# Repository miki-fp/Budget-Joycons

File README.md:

# Budget-Joycons
Custom Split Controller, inspired by Nintendo Joycons

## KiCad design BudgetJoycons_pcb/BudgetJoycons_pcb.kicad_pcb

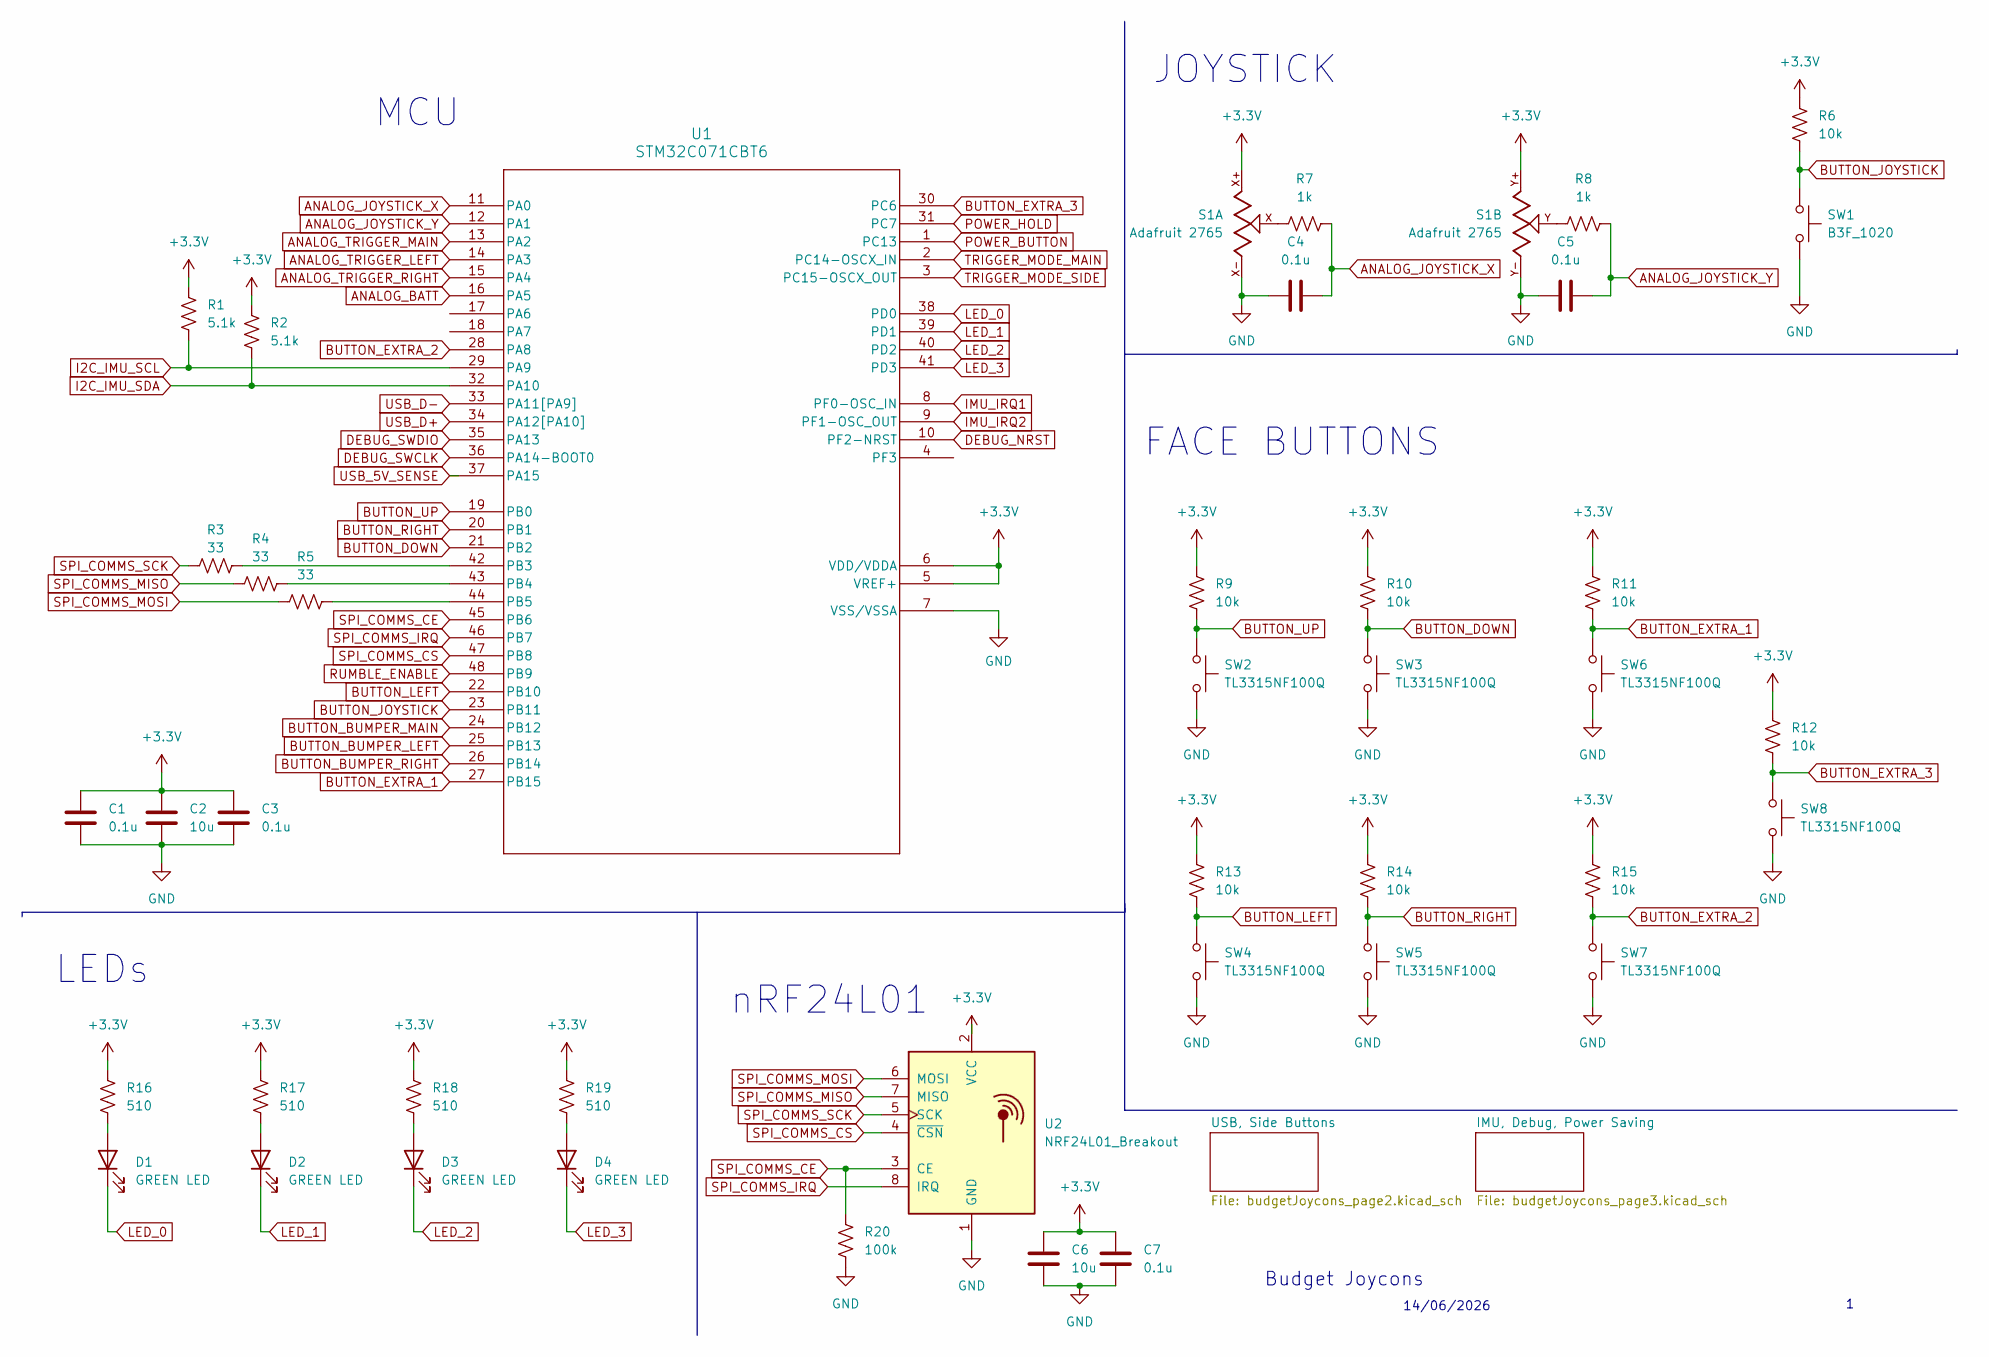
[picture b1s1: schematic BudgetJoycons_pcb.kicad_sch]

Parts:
C1, C3, C4, C5, C7: 0.1u; C_0603_1608Metric_Pad1.08x0.95mm_HandSolder
C2, C6: 10u; C_0805_2012Metric_Pad1.18x1.45mm_HandSolder
D1, D2, D3, D4: GREEN LED; LED_0805_2012Metric_Pad1.15x1.40mm_HandSolder
R1, R2: 5.1k; R_0603_1608Metric_Pad0.98x0.95mm_HandSolder
R3, R4, R5: 33; R_0603_1608Metric_Pad0.98x0.95mm_HandSolder
R6, R9, R10, R11, R12, R13, R14, R15: 10k; R_0603_1608Metric_Pad0.98x0.95mm_HandSolder
R7, R8: 1k; R_0603_1608Metric_Pad0.98x0.95mm_HandSolder
R16, R17, R18, R19: 510; R_0805_2012Metric_Pad1.20x1.40mm_HandSolder
R20: 100k; R_0603_1608Metric_Pad0.98x0.95mm_HandSolder
S1: Adafruit 2765; Adafruit_Joystick_2765
SW1: B3F_1020; B3F-1020
SW2, SW3, SW4, SW5, SW6, SW7, SW8: TL3315NF100Q; SW_TL3315NF100Q
U1: STM32C071CBT6; LQFP48_1_STM-M
U2: NRF24L01_Breakout; nRF24L01_Breakout

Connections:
+3.3V: C1.1, C2.1, C3.1, C6.1, C7.1, R1.1, R2.1, R6.1, R9.1, R10.1, R11.1, R12.1, R13.1, R14.1, R15.1, R16.1, R17.1, R18.1, R19.1, S1.X+, S1.Y+, U1.5 (VREF+), U1.6 (VDD/VDDA), U2.2 (VCC); also elsewhere on the board
ANALOG_BATT: U1.16 (PA5); also elsewhere on the board
ANALOG_JOYSTICK_X: C4.2, R7.2, U1.11 (PA0)
ANALOG_JOYSTICK_Y: C5.2, R8.2, U1.12 (PA1)
ANALOG_TRIGGER_LEFT: U1.14 (PA3); also elsewhere on the board
ANALOG_TRIGGER_MAIN: U1.13 (PA2); also elsewhere on the board
ANALOG_TRIGGER_RIGHT: U1.15 (PA4); also elsewhere on the board
BUTTON_BUMPER_LEFT: U1.25 (PB13); also elsewhere on the board
BUTTON_BUMPER_MAIN: U1.24 (PB12); also elsewhere on the board
BUTTON_BUMPER_RIGHT: U1.26 (PB14); also elsewhere on the board
BUTTON_DOWN: R10.2, SW3.1, U1.21 (PB2)
BUTTON_EXTRA_1: R11.2, SW6.1, U1.27 (PB15)
BUTTON_EXTRA_2: R15.2, SW7.1, U1.28 (PA8)
BUTTON_EXTRA_3: R12.2, SW8.1, U1.30 (PC6)
BUTTON_JOYSTICK: R6.2, SW1.1, U1.23 (PB11)
BUTTON_LEFT: R13.2, SW4.1, U1.22 (PB10)
BUTTON_RIGHT: R14.2, SW5.1, U1.20 (PB1)
BUTTON_UP: R9.2, SW2.1, U1.19 (PB0)
DEBUG_NRST: U1.10 (PF2-NRST); also elsewhere on the board
DEBUG_SWCLK: U1.36 (PA14-BOOT0); also elsewhere on the board
DEBUG_SWDIO: U1.35 (PA13); also elsewhere on the board
GND: C1.2, C2.2, C3.2, C4.1, C5.1, C6.2, C7.2, R20.2, S1.X-, S1.Y-, SW1.2, SW2.2, SW3.2, SW4.2, SW5.2, SW6.2, SW7.2, SW8.2, U1.7 (VSS/VSSA), U2.1 (GND); also elsewhere on the board
I2C_IMU_SCL: R1.2, U1.29 (PA9); also elsewhere on the board
I2C_IMU_SDA: R2.2, U1.32 (PA10); also elsewhere on the board
IMU_IRQ1: U1.8 (PF0-OSC_IN); also elsewhere on the board
IMU_IRQ2: U1.9 (PF1-OSC_OUT); also elsewhere on the board
LED_0: D1.1 (K), U1.38 (PD0)
LED_1: D2.1 (K), U1.39 (PD1)
LED_2: D3.1 (K), U1.40 (PD2)
LED_3: D4.1 (K), U1.41 (PD3)
unnamed: D1.2 (A), R16.2
unnamed: D2.2 (A), R17.2
unnamed: D3.2 (A), R18.2
unnamed: D4.2 (A), R19.2
unnamed: R7.1, S1.X
unnamed: R8.1, S1.Y
unnamed: R3.1, U1.42 (PB3)
unnamed: R4.1, U1.43 (PB4)
unnamed: R5.1, U1.44 (PB5)
POWER_BUTTON: U1.1 (PC13); also elsewhere on the board
POWER_HOLD: U1.31 (PC7); also elsewhere on the board
RUMBLE_ENABLE: U1.48 (PB9); also elsewhere on the board
SPI_COMMS_CE: R20.1, U1.45 (PB6), U2.3 (CE)
SPI_COMMS_CS: U1.47 (PB8), U2.4 (~CSN)
SPI_COMMS_IRQ: U1.46 (PB7), U2.8 (IRQ)
SPI_COMMS_MISO: R4.2, U2.7 (MISO)
SPI_COMMS_MOSI: R5.2, U2.6 (MOSI)
SPI_COMMS_SCK: R3.2, U2.5 (SCK)
TRIGGER_MODE_MAIN: U1.2 (PC14-OSCX_IN); also elsewhere on the board
TRIGGER_MODE_SIDE: U1.3 (PC15-OSCX_OUT); also elsewhere on the board
USB_5V_SENSE: U1.37 (PA15); also elsewhere on the board
USB_D+: U1.34 (PA12[PA10]); also elsewhere on the board
USB_D-: U1.33 (PA11[PA9]); also elsewhere on the board

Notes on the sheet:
14/06/2026
FACE BUTTONS
MCU
JOYSTICK
Budget Joycons
LEDs
nRF24L01

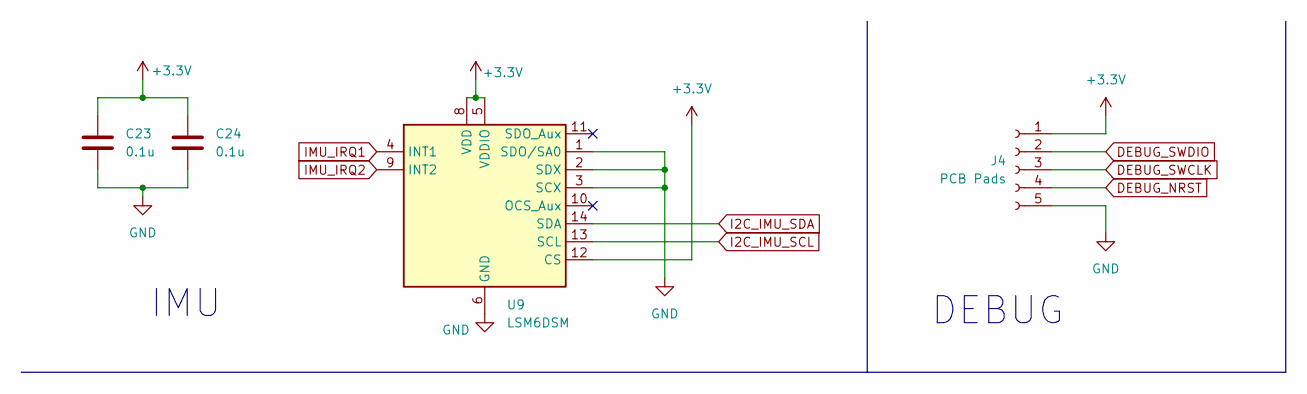
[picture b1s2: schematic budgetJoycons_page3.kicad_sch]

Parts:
C23, C24: 0.1u; C_0603_1608Metric_Pad1.08x0.95mm_HandSolder
J4: PCB Pads; Edge_2.54mm_Pads
U9: LSM6DSM; LGA-14_3x2.5mm_P0.5mm_LayoutBorder3x4y

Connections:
+3.3V: C23.2, C24.2, J4.1, U9.5 (VDDIO), U9.8 (VDD), U9.12 (CS); also elsewhere on the board
DEBUG_NRST: J4.4; also elsewhere on the board
DEBUG_SWCLK: J4.3; also elsewhere on the board
DEBUG_SWDIO: J4.2; also elsewhere on the board
GND: C23.1, C24.1, J4.5, U9.1 (SDO/SA0), U9.2 (SDX), U9.3 (SCX), U9.6 (GND), U9.7 (GND); also elsewhere on the board
I2C_IMU_SCL: U9.13 (SCL); also elsewhere on the board
I2C_IMU_SDA: U9.14 (SDA); also elsewhere on the board
IMU_IRQ1: U9.4 (INT1); also elsewhere on the board
IMU_IRQ2: U9.9 (INT2); also elsewhere on the board

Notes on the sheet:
DEBUG
IMU

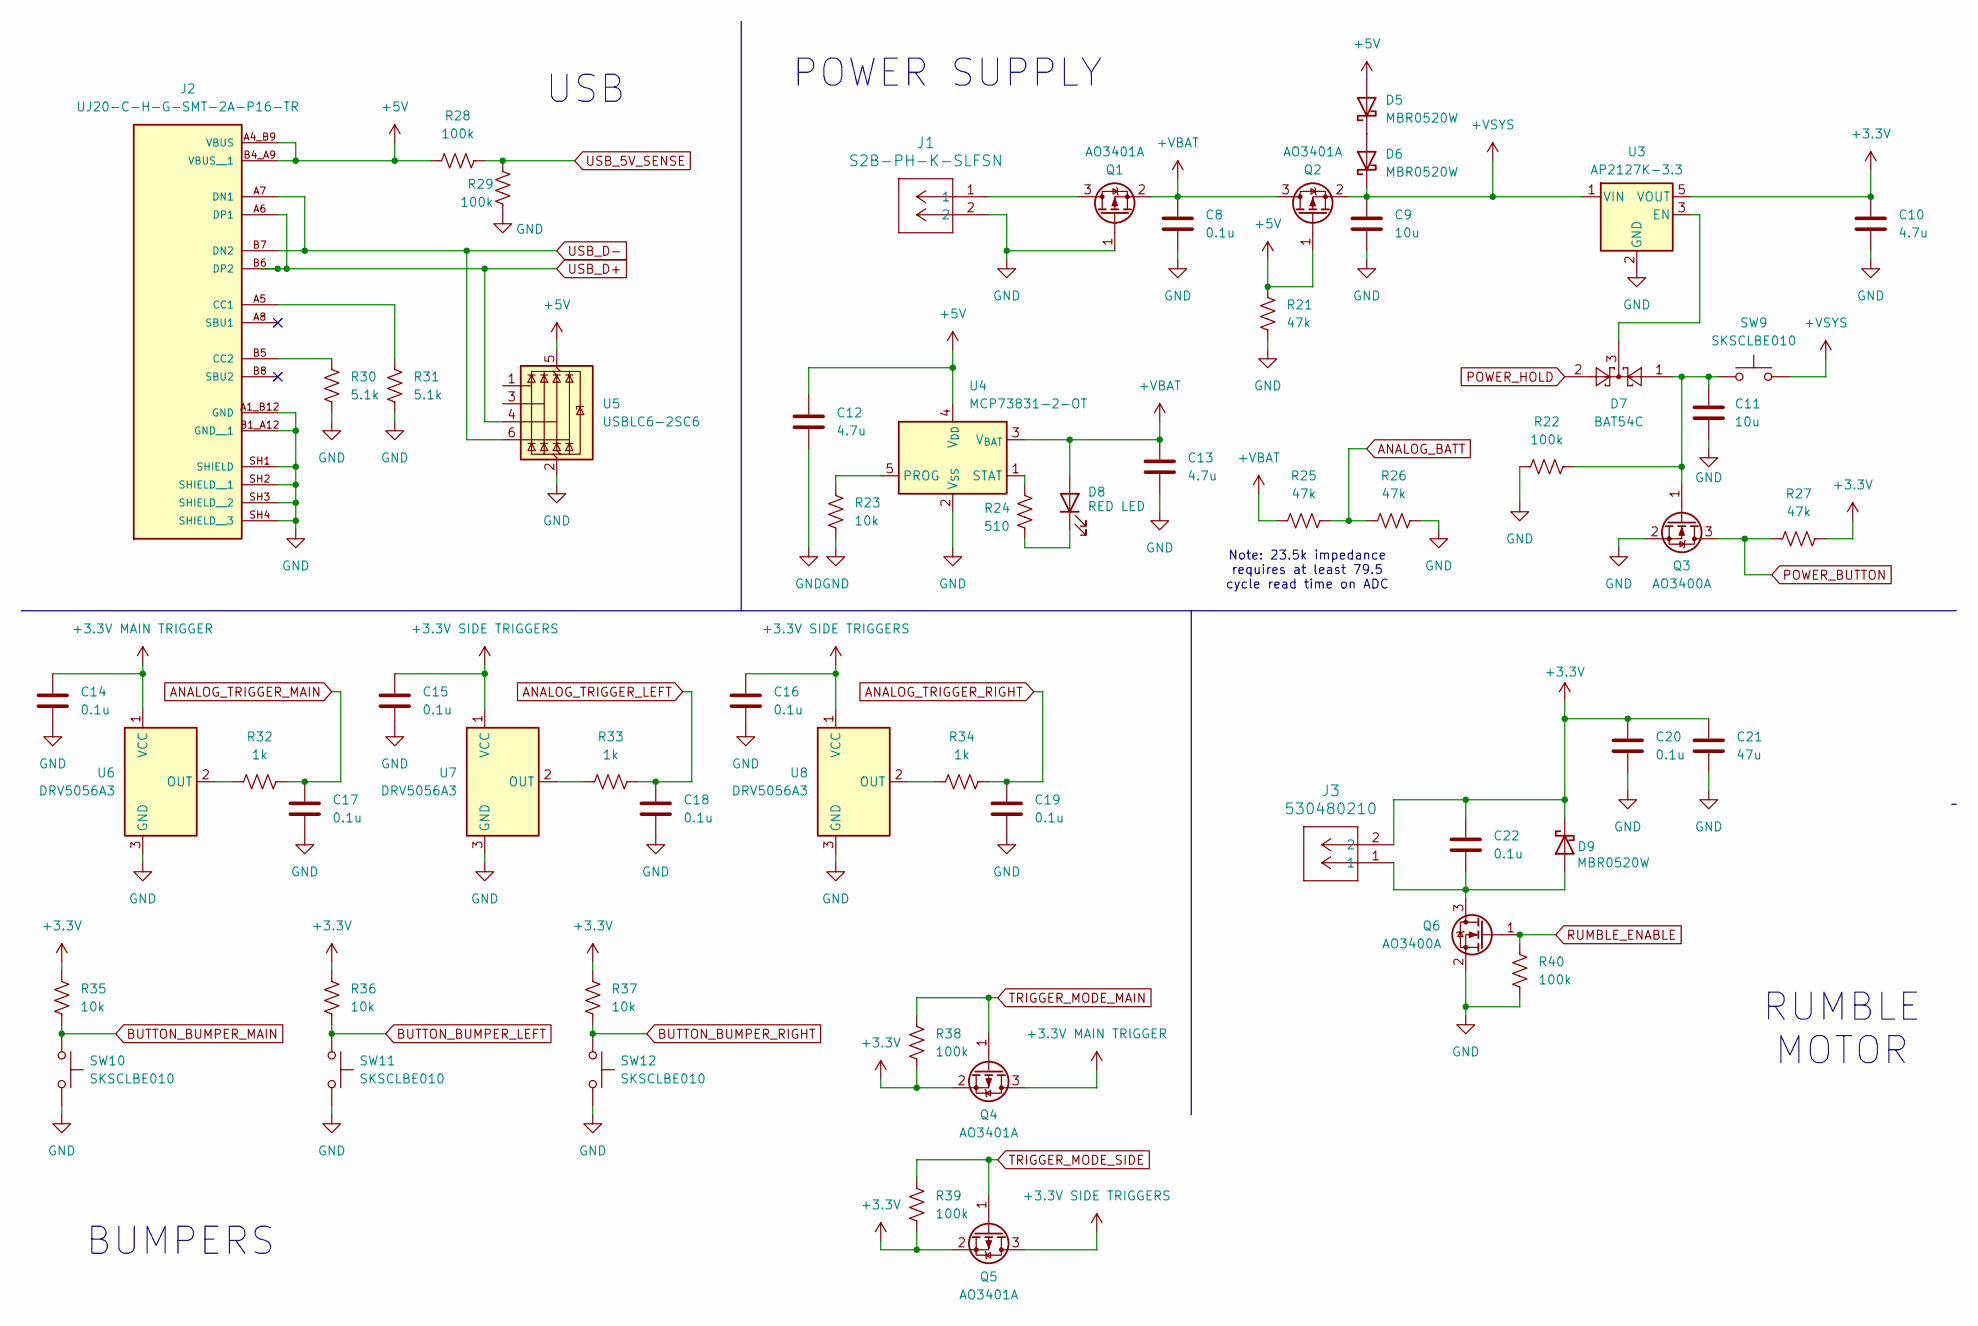
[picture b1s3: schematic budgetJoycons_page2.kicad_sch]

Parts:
C8, C14, C15, C16, C17, C18, C19, C20, C22: 0.1u; C_0603_1608Metric_Pad1.08x0.95mm_HandSolder
C9, C11: 10u; C_0805_2012Metric_Pad1.18x1.45mm_HandSolder
C10, C12, C13: 4.7u; C_0603_1608Metric_Pad1.08x0.95mm_HandSolder
C21: 47u; C_1206_3216Metric_Pad1.33x1.80mm_HandSolder
D5, D6, D9: MBR0520W; D_SOD-123
D7: BAT54C; SOT-23
D8: RED LED; LED_0805_2012Metric_Pad1.15x1.40mm_HandSolder
J1: S2B-PH-K-SLFSN; CONN_S2B-PH-K-S_JST
J2: UJ20-C-H-G-SMT-2A-P16-TR; SAMESKY_UJ20-C-H-G-SMT-2A-P16-TR; PARTREV 1.0
J3: 530480210; CONN02_530480210_MOL
Q1, Q2, Q4, Q5: AO3401A; SOT-23
Q3, Q6: AO3400A; SOT-23
R21, R25, R26, R27: 47k; R_0603_1608Metric_Pad0.98x0.95mm_HandSolder
R22, R28, R29, R38, R39, R40: 100k; R_0603_1608Metric_Pad0.98x0.95mm_HandSolder
R23, R35, R36, R37: 10k; R_0603_1608Metric_Pad0.98x0.95mm_HandSolder
R24: 510; R_0805_2012Metric_Pad1.20x1.40mm_HandSolder
R30, R31: 5.1k; R_0603_1608Metric_Pad0.98x0.95mm_HandSolder
R32, R33, R34: 1k; R_0603_1608Metric_Pad0.98x0.95mm_HandSolder
SW9, SW10, SW11, SW12: SKSCLBE010; SKSCLDE010
U3: AP2127K-3.3; SOT-23-5
U4: MCP73831-2-OT; SOT-23-5
U5: USBLC6-2SC6; SOT-23-6
U6, U7, U8: DRV5056A3; SOT-23-3

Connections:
+3.3V: C10.1, C20.1, C21.1, C22.1, D9.1 (K), J3.2, Q4.2 (S), Q5.2 (S), R27.2, R35.1, R36.1, R37.1, R38.2, R39.2, U3.5 (VOUT); also elsewhere on the board
+3.3V MAIN TRIGGER: C14.1, Q4.3 (D), U6.1 (VCC)
+3.3V SIDE TRIGGERS: C15.1, C16.1, Q5.3 (D), U7.1 (VCC), U8.1 (VCC)
+5V: C12.1, D5.2 (A), J2.A4_B9 (VBUS), J2.B4_A9 (VBUS__1), Q2.1 (G), R21.1, R28.2, U4.4 (V_{DD}), U5.5 (VBUS)
+VBAT: C8.1, C13.1, D8.2 (A), Q1.2 (S), Q2.3 (D), R25.1, U4.3 (V_{BAT})
+VSYS: C9.1, D6.1 (K), Q2.2 (S), SW9.2, U3.1 (VIN)
ANALOG_BATT: R25.2, R26.2; also elsewhere on the board
ANALOG_TRIGGER_LEFT: C18.1, R33.2; also elsewhere on the board
ANALOG_TRIGGER_MAIN: C17.1, R32.2; also elsewhere on the board
ANALOG_TRIGGER_RIGHT: C19.1, R34.2; also elsewhere on the board
BUTTON_BUMPER_LEFT: R36.2, SW11.1; also elsewhere on the board
BUTTON_BUMPER_MAIN: R35.2, SW10.1; also elsewhere on the board
BUTTON_BUMPER_RIGHT: R37.2, SW12.1; also elsewhere on the board
GND: C8.2, C9.2, C10.2, C11.2, C12.2, C13.2, C14.2, C15.2, C16.2, C17.2, C18.2, C19.2, C20.2, C21.2, J1.2, J2.A1_B12 (GND), J2.B1_A12 (GND__1), J2.SH1 (SHIELD), J2.SH2 (SHIELD__1), J2.SH3 (SHIELD__2), J2.SH4 (SHIELD__3), Q1.1 (G), Q3.2 (S), Q6.2 (S), R21.2, R22.1, R23.2, R26.1, R29.2, R30.2, R31.2, R40.2, SW10.2, SW11.2, SW12.2, U3.2 (GND), U4.2 (V_{SS}), U5.2 (GND), U6.3 (GND), U7.3 (GND), U8.3 (GND); also elsewhere on the board
unnamed: D5.1 (K), D6.2 (A)
unnamed: D8.1 (K), R24.2
unnamed: C22.2, D9.2 (A), J3.1, Q6.3 (D)
unnamed: J2.A5 (CC1), R31.1
unnamed: J2.B5 (CC2), R30.1
unnamed: J1.1, Q1.3 (D)
unnamed: C11.1, D7.1, Q3.1 (G), R22.2, SW9.1
unnamed: D7.3, U3.3 (EN)
unnamed: R23.1, U4.5 (PROG)
unnamed: R24.1, U4.1 (STAT)
unnamed: R32.1, U6.2 (OUT)
unnamed: R33.1, U7.2 (OUT)
unnamed: R34.1, U8.2 (OUT)
POWER_BUTTON: Q3.3 (D), R27.1; also elsewhere on the board
POWER_HOLD: D7.2; also elsewhere on the board
RUMBLE_ENABLE: Q6.1 (G), R40.1; also elsewhere on the board
TRIGGER_MODE_MAIN: Q4.1 (G), R38.1; also elsewhere on the board
TRIGGER_MODE_SIDE: Q5.1 (G), R39.1; also elsewhere on the board
USB_5V_SENSE: R28.1, R29.1; also elsewhere on the board
USB_D+: J2.A6 (DP1), J2.B6 (DP2), U5.4 (I/O3); also elsewhere on the board
USB_D-: J2.A7 (DN1), J2.B7 (DN2), U5.6 (I/O4); also elsewhere on the board

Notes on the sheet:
BUMPERS
USB
POWER SUPPLY
Note: 23.5k impedance requires at least 79.5 cycle read time on ADC
RUMBLE MOTOR

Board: 4 copper layers, 105 parts (37 on the bottom side), 71 nets, no tracks yet.

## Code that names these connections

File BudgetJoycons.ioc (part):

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Mcu.Name=STM32C071CBTx
Mcu.Package=LQFP48_GP
Mcu.UserName=STM32C071CBTx
PA0.GPIOParameters=GPIO_Label
PA0.GPIO_Label=ANALOG_JOYSTICK_X
PA0.Mode=IN0
PA0.Signal=ADC1_IN0
PA1.GPIOParameters=GPIO_Label
PA1.GPIO_Label=ANALOG_JOYSTICK_Y
PA1.Mode=IN1
PA1.Signal=ADC1_IN1
PA10.GPIOParameters=GPIO_Label
PA10.GPIO_Label=I2C_IMU_SDA
PA10.Mode=I2C
PA10.Signal=I2C1_SDA
PA11\ [PA9].Mode=Device
PA11\ [PA9].Signal=USB_DM
PA12\ [PA10].Mode=Device
PA12\ [PA10].Signal=USB_DP
PA13.Mode=Serial_Wire
PA13.Signal=DEBUG_SWDIO
PA14-BOOT0.Mode=Serial_Wire
PA14-BOOT0.Signal=DEBUG_SWCLK
PA15.GPIOParameters=GPIO_Label
PA15.GPIO_Label=USB_5V_SENSE
PA15.Signal=GPIO_Input
PA2.GPIOParameters=GPIO_Label
PA2.GPIO_Label=ANALOG_TRIGGER_MAIN
PA2.Mode=IN2
PA2.Signal=ADC1_IN2
PA3.GPIOParameters=GPIO_Label
PA3.GPIO_Label=ANALOG_TRIGGER_LEFT
PA3.Mode=IN3
PA3.Signal=ADC1_IN3
PA4.GPIOParameters=GPIO_Label
PA4.GPIO_Label=ANALOG_TRIGGER_RIGHT
PA4.Mode=IN4
PA4.Signal=ADC1_IN4
PA5.GPIOParameters=GPIO_Label
PA5.GPIO_Label=ANALOG_BATT
PA5.Mode=IN5
PA5.Signal=ADC1_IN5
PA8.GPIOParameters=GPIO_Label
PA8.GPIO_Label=BUTTON_EXTRA_2
PA8.Signal=GPIO_Input
PA9.GPIOParameters=GPIO_Label
PA9.GPIO_Label=I2C_IMU_SCL
PA9.Mode=I2C
PA9.Signal=I2C1_SCL
PB0.GPIOParameters=GPIO_Label
PB0.GPIO_Label=BUTTON_UP
PB0.Signal=GPIO_Input
PB1.GPIOParameters=GPIO_Label
PB1.GPIO_Label=BUTTON_RIGHT
PB1.Signal=GPIO_Input
PB10.GPIOParameters=GPIO_Label
PB10.GPIO_Label=BUTTON_LEFT
PB10.Signal=GPIO_Input
PB11.GPIOParameters=GPIO_Label
PB11.GPIO_Label=BUTTON_JOYSTICK
PB11.Signal=GPIO_Input
PB12.GPIOParameters=GPIO_Label
PB12.GPIO_Label=BUTTON_BUMPER_MAIN
PB12.Signal=GPIO_Input
PB13.GPIOParameters=GPIO_Label
PB13.GPIO_Label=BUTTON_BUMPER_LEFT
PB13.Signal=GPIO_Input
PB14.GPIOParameters=GPIO_Label
PB14.GPIO_Label=BUTTON_BUMPER_RIGHT
PB14.Signal=GPIO_Input
PB15.GPIOParameters=GPIO_Label
PB15.GPIO_Label=BUTTON_EXTRA_1
PB15.Signal=GPIO_Input
PB2.GPIOParameters=GPIO_Label
PB2.GPIO_Label=BUTTON_DOWN
PB2.Signal=GPIO_Input
PB3.GPIOParameters=GPIO_Label
PB3.GPIO_Label=SPI_COMMS_SCK
PB3.Mode=Full_Duplex_Master
PB3.Signal=SPI1_SCK
PB4.GPIOParameters=GPIO_Label
PB4.GPIO_Label=SPI_COMMS_MISO
PB4.Mode=Full_Duplex_Master
PB4.Signal=SPI1_MISO
PB5.GPIOParameters=GPIO_Label
PB5.GPIO_Label=SPI_COMMS_MOSI
PB5.Mode=Full_Duplex_Master
PB5.Signal=SPI1_MOSI
PB6.GPIOParameters=GPIO_Label
PB6.GPIO_Label=SPI_COMMS_CE
PB6.Signal=GPIO_Output
PB7.GPIOParameters=GPIO_Label
PB7.GPIO_Label=SPI_COMMS_IRQ
PB7.Signal=GPIO_Input
PB8.GPIOParameters=GPIO_Label
PB8.GPIO_Label=SPI_COMMS_CS
PB8.Signal=GPIO_Output
PB9.GPIOParameters=GPIO_Label
PB9.GPIO_Label=RUMBLE_ENABLE
PB9.Signal=GPIO_Output
PC13.GPIOParameters=GPIO_Label
PC13.GPIO_Label=POWER_BUTTON
PC13.Signal=GPIO_Input
PC14-OSCX_IN(PC14).GPIOParameters=GPIO_Label
PC14-OSCX_IN(PC14).GPIO_Label=TRIGGER_MODE_1
PC14-OSCX_IN(PC14).Signal=GPIO_Output
PC15-OSCX_OUT(PC15).GPIOParameters=GPIO_Label
PC15-OSCX_OUT(PC15).GPIO_Label=TRIGGER_MODE_2
PC15-OSCX_OUT(PC15).Signal=GPIO_Output
PC6.GPIOParameters=GPIO_Label
PC6.GPIO_Label=BUTTON_EXTRA_3
PC6.Signal=GPIO_Input
PC7.GPIOParameters=GPIO_Label
PC7.GPIO_Label=POWER_HOLD
PC7.Signal=GPIO_Output
PD0.GPIOParameters=GPIO_Label
PD0.GPIO_Label=LED_0
PD0.Signal=GPIO_Output
PD1.GPIOParameters=GPIO_Label
PD1.GPIO_Label=LED_1
PD1.Signal=GPIO_Output
PD2.GPIOParameters=GPIO_Label
PD2.GPIO_Label=LED_2
PD2.Signal=GPIO_Output
PD3.GPIOParameters=GPIO_Label
PD3.GPIO_Label=LED_3
PD3.Signal=GPIO_Output
PF0-OSC_IN(PF0).GPIOParameters=GPIO_Label
PF0-OSC_IN(PF0).GPIO_Label=IMU_IRQ1
PF0-OSC_IN(PF0).Signal=GPIO_Input
PF1-OSC_OUT(PF1).GPIOParameters=GPIO_Label
PF1-OSC_OUT(PF1).GPIO_Label=IMU_IRQ2
PF1-OSC_OUT(PF1).Signal=GPIO_Input
RCC.HSE_VALUE=8000000
RCC.SYSCLKFreq_VALUE=12000000
board=custom

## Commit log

2026-06-21 Completed Schematic
2026-06-22 Right PCB update

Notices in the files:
parts and their libraries:
Copyright 2016 Accelerated Designs. All rights reserved.
